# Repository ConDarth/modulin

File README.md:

# Modulin

This repository holds all data for th modulin I am building. The concept behind this design is to make a fully analog synthesizer using only standard components, with a fun control system based on a violin. This project is mostly based on a design Martin Molin of Wintergatan. An explanation of his design can be found [here](https://www.youtube.com/watch?v=MUdWeBYe3GY). 

My goal in improving this design is to make it more accessible. His design uses 9 or so prebuilt modules meant for modular synthesizers, each of which costs in the range of 70$+ making the instrument quite expensive for a diy build. I took inspiration from the modular synth DIY community to instead try and build the necessary modules from scratch using only much cheaper standard electronics components. The components I am limiting myself to are resistors, capacitors, inductors/transformers, diodes, transistors (both BJT and FET), op amps and linear voltage regulators.

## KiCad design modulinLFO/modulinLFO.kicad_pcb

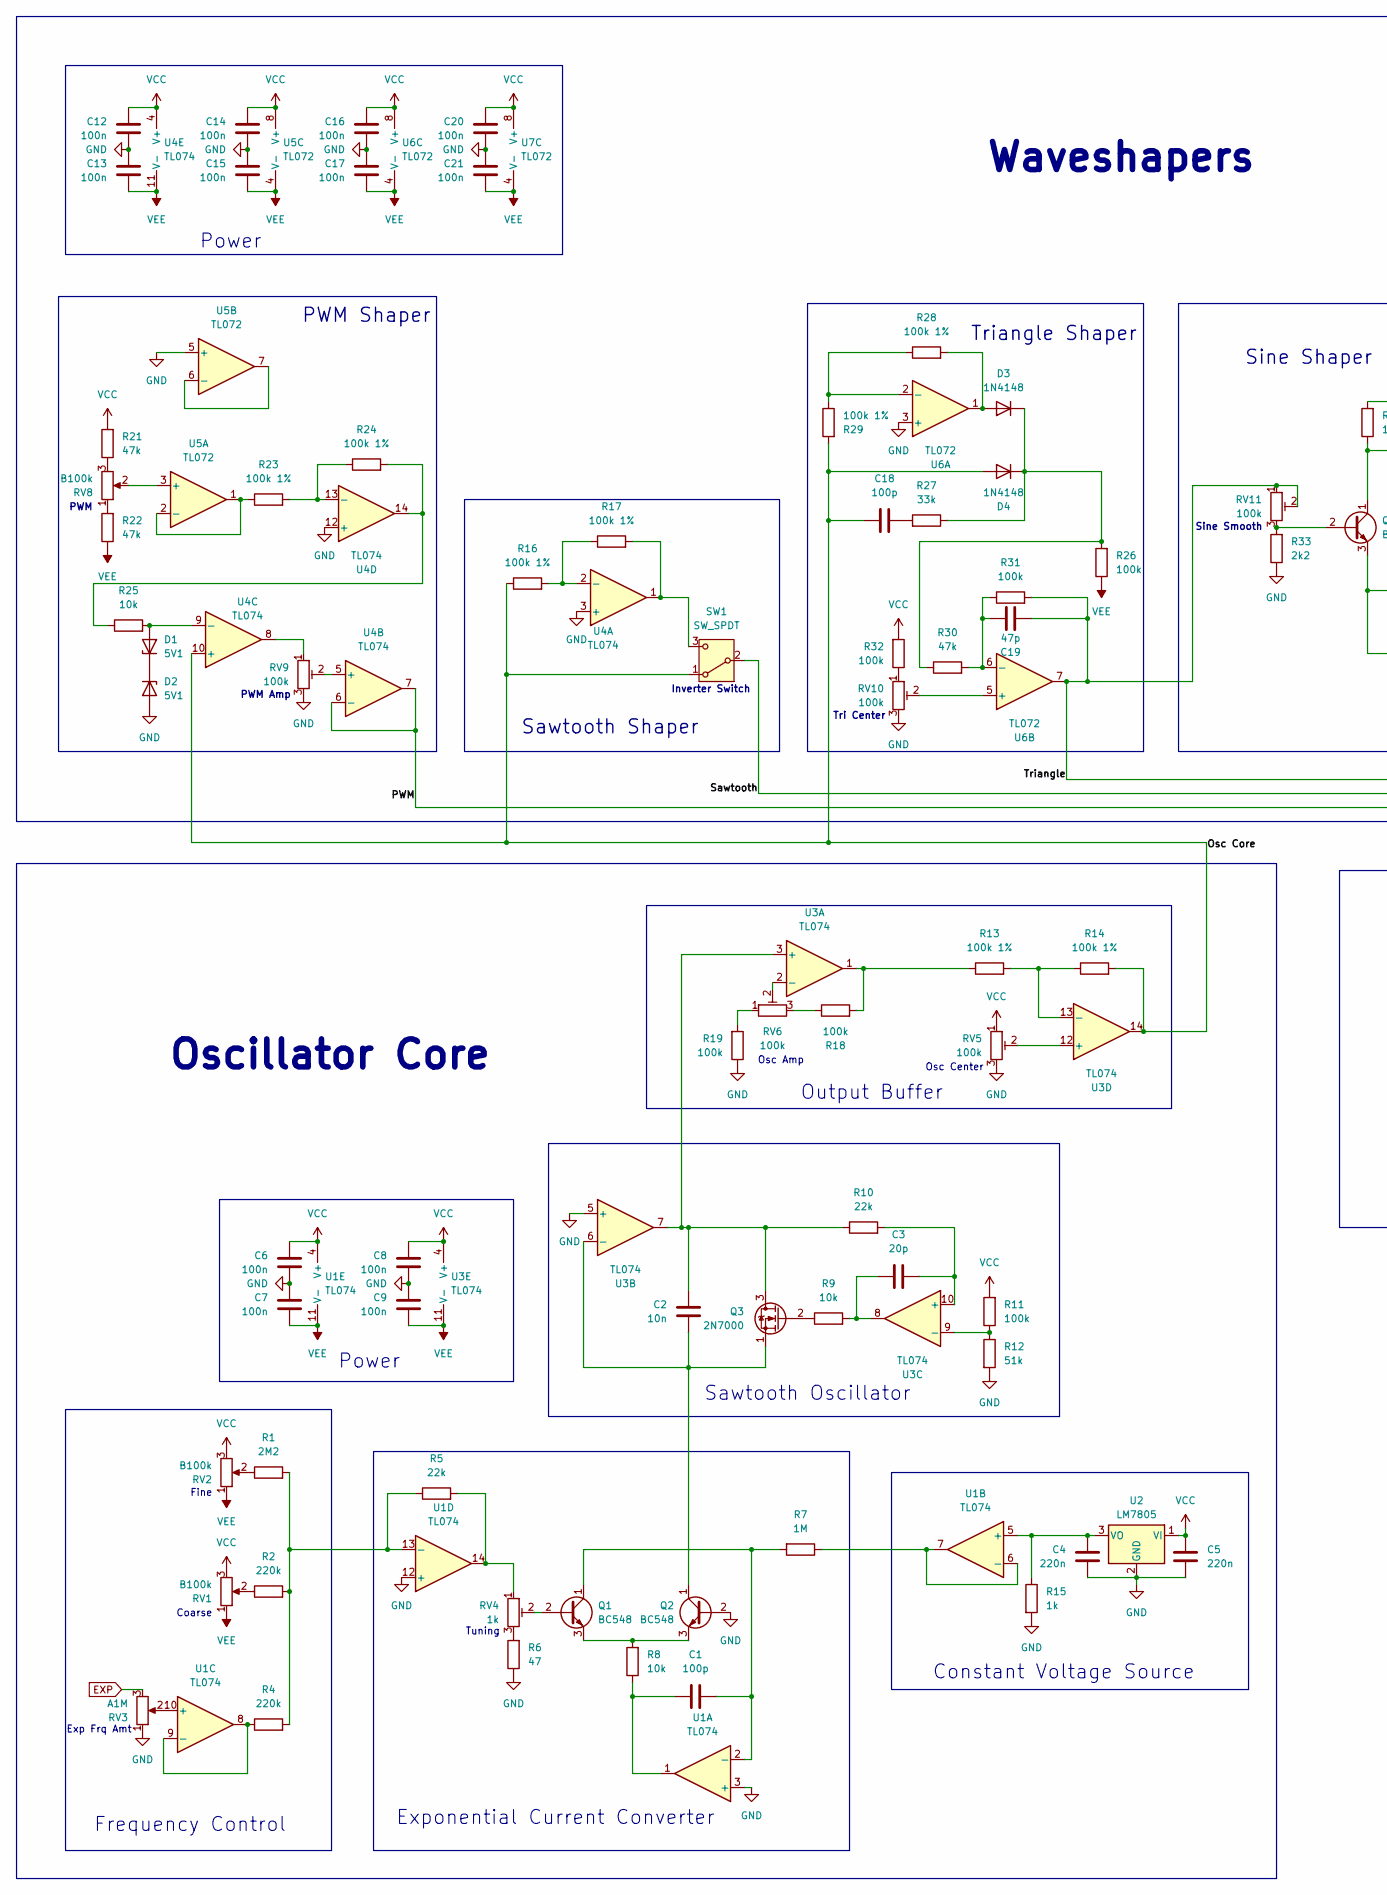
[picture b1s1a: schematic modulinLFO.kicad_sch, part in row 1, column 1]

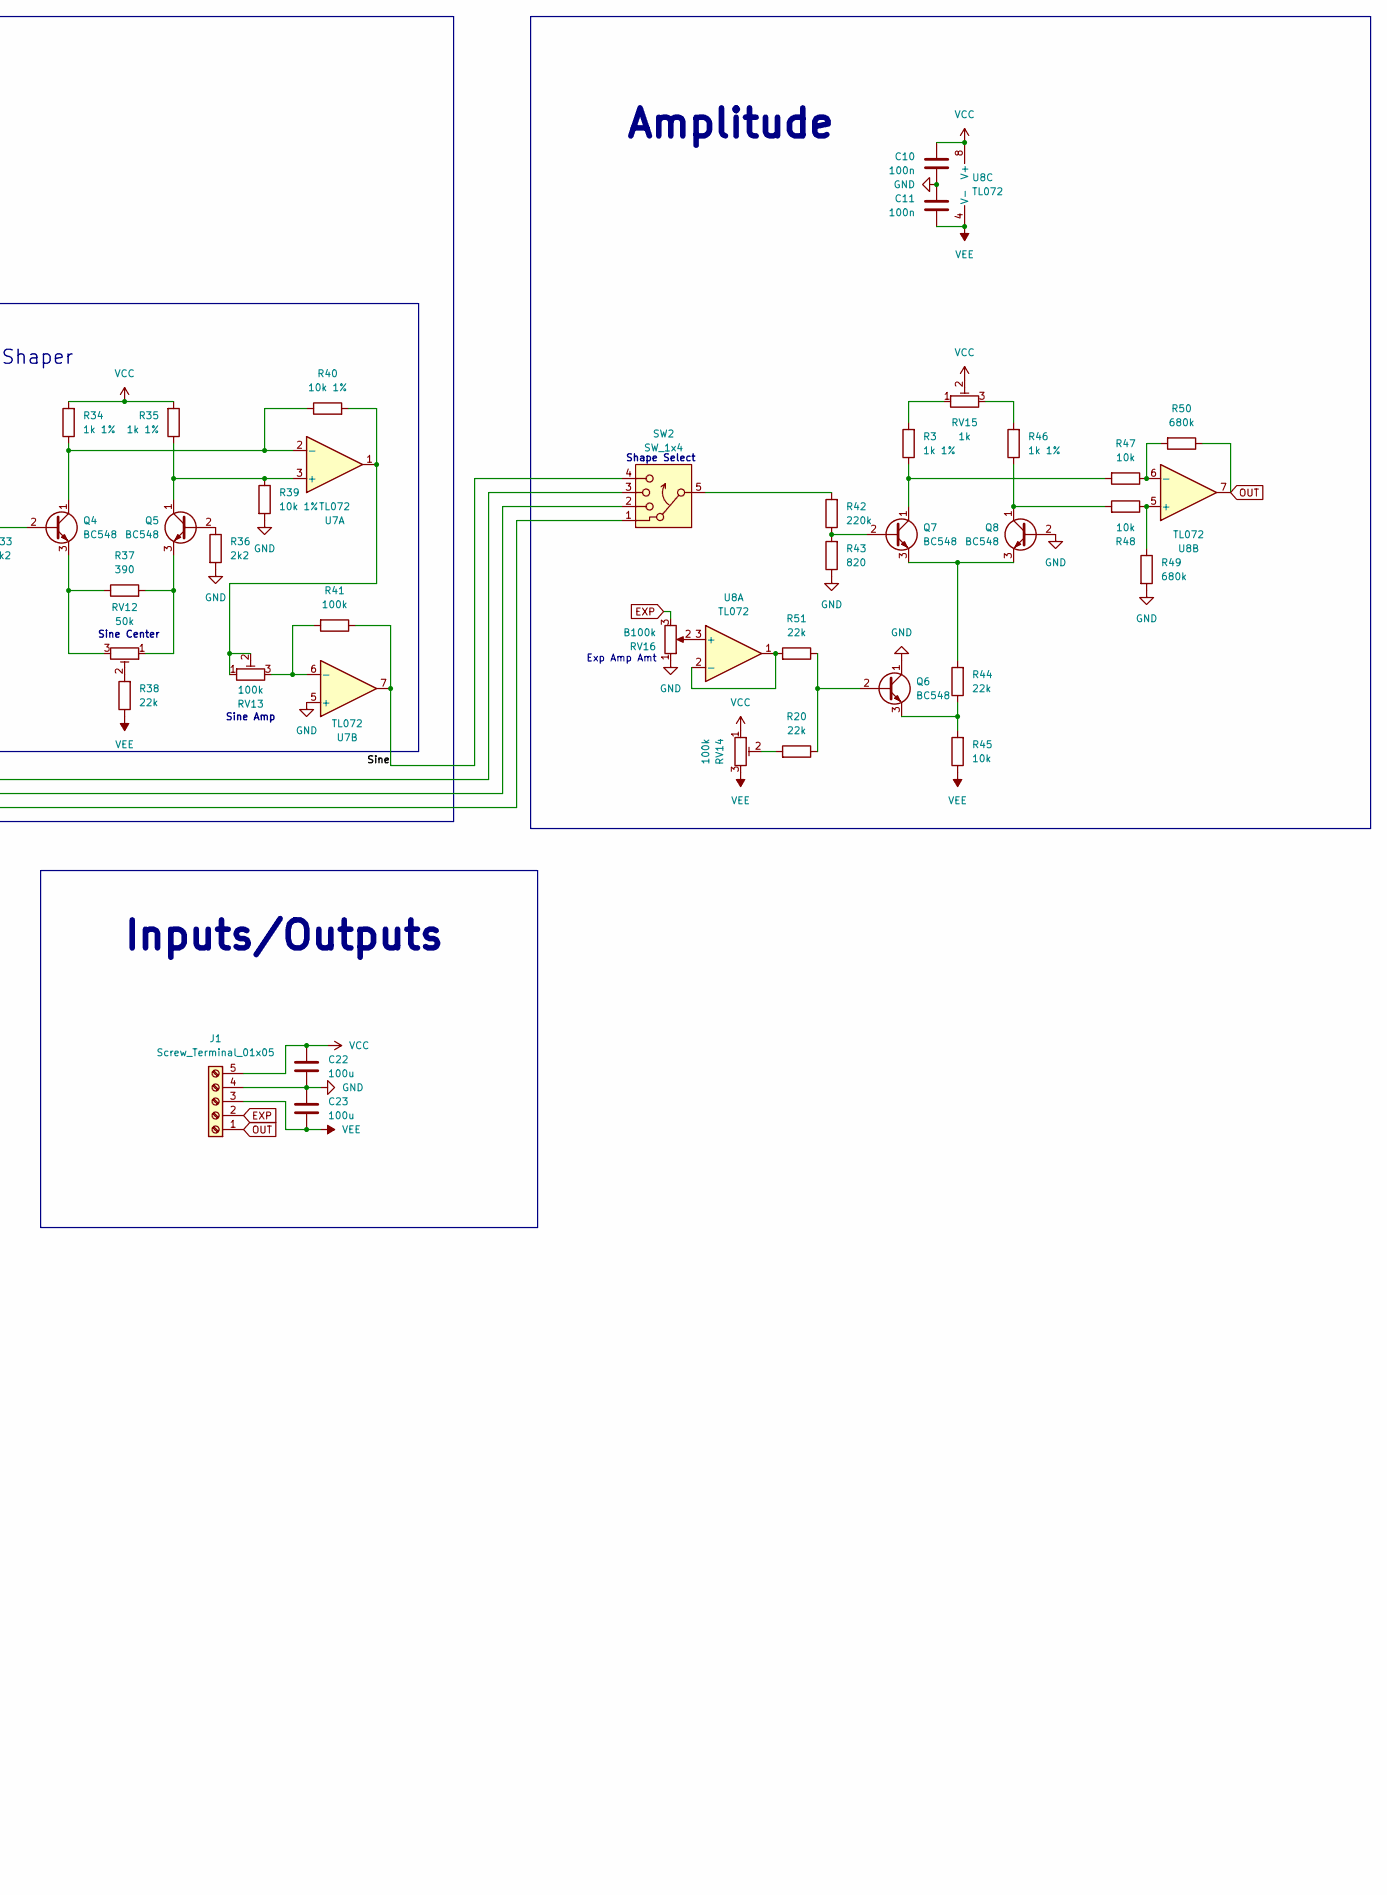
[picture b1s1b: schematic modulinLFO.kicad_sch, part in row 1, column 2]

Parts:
C1: 100p; C_Axial_P5.00mm_CNC
C2: 10n; C_Rect_P5.00mm_CNC
C3: 20p; C_Axial_P5.00mm_CNC
C4, C5: 220n; C_Axial_P5.00mm_CNC
C6, C7, C8, C9, C10, C11, C12, C13, C14, C15, C16, C17, C20, C21: 100n; C_Axial_P5.00mm_CNC
C18: 100p; C_Rect_P5.00mm_CNC
C19: 47p; C_Rect_P5.00mm_CNC
C22, C23: 100u; C_Radial_Polarized_P2.5mm_CNC
D1: 5V1; D_P2.54mm_CNC
D2: 5V1; D_P5.08mm_CNC
D3, D4: 1N4148; D_P7.62mm_CNC
J1: Screw_Terminal_01x05; TerminalBlock_1x5_CNC
Q1, Q2, Q4, Q5, Q6, Q7, Q8: BC548; TO-92_CNC
Q3: 2N7000; TO-92_CNC
R1: 2M2; R_10.16mm_CNC
R2, R42: 220k; R_10.16mm_CNC
R3, R46: 1k 1%; R_7.62mm_CNC
R4: 220k; R_2.54mm_CNC
R5: 22k; R_2.54mm_CNC
R6: 47; R_5.08mm_CNC
R7: 1M; R_10.16mm_CNC
R8, R9, R25, R45, R47, R48: 10k; R_10.16mm_CNC
R10, R38, R44, R51: 22k; R_10.16mm_CNC
R11: 100k; R_7.62mm_CNC
R12: 51k; R_5.08mm_CNC
R13, R16, R23: 100k 1%; R_10.16mm_CNC
R14, R17, R24, R28: 100k 1%; R_2.54mm_CNC
R15: 1k; R_7.62mm_CNC
R18, R31: 100k; R_2.54mm_CNC
R19, R41: 100k; R_2.54mm_CNC_Alt
R20: 22k; R_7.62mm_CNC
R21: 47k; R_7.62mm_CNC
R22, R30: 47k; R_10.16mm_CNC
R26, R32: 100k; R_10.16mm_CNC
R27: 33k; R_2.54mm_CNC_Alt
R29: 100k 1%; R_7.62mm_CNC
R33, R36: 2k2; R_10.16mm_CNC
R34, R35: 1k 1%; R_10.16mm_CNC
R37: 390; R_5.08mm_CNC
R39: 10k 1%; R_10.16mm_CNC
R40: 10k 1%; R_2.54mm_CNC_Alt
R43: 820; R_10.16mm_CNC
R49: 680k; R_10.16mm_CNC
R50: 680k; R_7.62mm_CNC
RV1, RV2, RV8, RV16: B100k; Potentiometer_PanelMount_CNC
RV3: A1M; Potentiometer_PanelMount_CNC
RV4, RV15: 1k; Potentiometer_Trim_CNC
RV5, RV6, RV9, RV10, RV11, RV13, RV14: 100k; Potentiometer_Trim_CNC
RV12: 50k; Potentiometer_Trim_CNC
SW1: SW_SPDT; SW_Slide_SPDT_H6.00mm_CNC
SW2: SW_1x4; SW_Slide_SP4T_H6.00mm_CNC
U1, U3, U4: TL074; DIP-14_CNC
U2: LM7805; TO-220_CNC
U5, U6, U7, U8: TL072; DIP-8_CNC

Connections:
/Osc Core: C18.1, D4.2 (A), R14.2, R16.1, R29.2, SW1.1 (A), U3.14, U4.10 (+)
/PWM: SW2.1, U4.6 (-), U4.7
/Sawtooth: SW1.2 (B), SW2.2
/Sine: R41.1, SW2.4, U7.7
/Triangle: C19.2, R31.2, RV11.1, RV11.2, SW2.3, U6.7
EXP: J1.2, RV3.3, RV16.3
GND: C4.1, C5.1, C6.2, C7.1, C8.2, C9.1, C10.2, C11.1, C12.2, C13.1, C14.2, C15.1, C16.2, C17.1, C20.2, C21.1, C22.1, C23.2, D2.2 (A), J1.4, Q2.2 (B), Q6.1 (C), Q8.2 (B), R6.1, R12.2, R15.2, R19.1, R33.1, R36.2, R39.2, R43.1, R49.2, RV3.1, RV5.3, RV9.3, RV10.3, RV16.1, U1.3 (+), U1.12 (+), U2.2 (GND), U3.5 (+), U4.3 (+), U4.12 (+), U5.5 (+), U6.3 (+), U7.5 (+)
unnamed: C1.1, R8.1, U1.1
unnamed: C3.1, R9.2, U3.8
unnamed: C18.2, R27.2
unnamed: D1.2 (A), R25.2, U4.9 (-)
unnamed: D1.1 (K), D2.1 (K)
unnamed: D3.2 (A), R28.2, U6.1
unnamed: D3.1 (K), D4.1 (K), R26.2, R27.1, R30.1
unnamed: Q1.2 (B), RV4.2
unnamed: C1.2, Q1.1 (C), R7.2, U1.2 (-)
unnamed: Q1.3 (E), Q2.3 (E), R8.2
unnamed: C2.2, Q2.1 (C), Q3.1 (S), U3.6 (-)
unnamed: C2.1, Q3.3 (D), R10.1, U3.3 (+), U3.7
unnamed: Q3.2 (G), R9.1
unnamed: Q4.2 (B), R33.2, RV11.3
unnamed: Q4.1 (C), R34.1, R40.1, U7.2 (-)
unnamed: Q4.3 (E), R37.1, RV12.3
unnamed: Q5.2 (B), R36.1
unnamed: Q5.1 (C), R35.1, R39.1, U7.3 (+)
unnamed: Q5.3 (E), R37.2, RV12.1
unnamed: Q6.2 (B), R20.1, R51.1
unnamed: Q6.3 (E), R44.1, R45.2
unnamed: Q7.2 (B), R42.1, R43.2
unnamed: Q7.1 (C), R3.1, R47.2
unnamed: Q7.3 (E), Q8.3 (E), R44.2
unnamed: Q8.1 (C), R46.1, R48.2
unnamed: R1.1, RV2.2
unnamed: R2.1, RV1.2
unnamed: R3.2, RV15.1
unnamed: R5.2, RV4.1, U1.14
unnamed: R6.2, RV4.3
unnamed: R13.1, R18.2, U3.1
unnamed: R18.1, RV6.3
unnamed: R19.2, RV6.1
unnamed: R20.2, RV14.2
unnamed: R21.1, RV8.3
unnamed: R22.2, RV8.1
unnamed: R24.2, R25.1, U4.14
unnamed: R32.1, RV10.1
unnamed: R38.2, RV12.2
unnamed: R40.2, RV13.1, RV13.2, U7.1
unnamed: R42.2, SW2.5
unnamed: R46.2, RV15.3
unnamed: RV9.1, U4.8
unnamed: R17.2, SW1.3 (C), U4.1
unnamed: C4.2, R15.1, U1.5 (+), U2.3 (VO)
unnamed: R7.1, U1.6 (-), U1.7
unnamed: RV3.2, U1.10 (+)
unnamed: R4.1, U1.8, U1.9 (-)
unnamed: R1.2, R2.2, R4.2, R5.1, U1.13 (-)
unnamed: RV6.2, U3.2 (-)
unnamed: C3.2, R10.2, U3.10 (+)
unnamed: R11.1, R12.1, U3.9 (-)
unnamed: RV5.2, U3.12 (+)
unnamed: R13.2, R14.1, U3.13 (-)
unnamed: R16.2, R17.1, U4.2 (-)
unnamed: RV9.2, U4.5 (+)
unnamed: R23.2, R24.1, U4.13 (-)
unnamed: RV8.2, U5.3 (+)
unnamed: R23.1, U5.1, U5.2 (-)
unnamed: U5.6 (-), U5.7
unnamed: R28.1, R29.1, U6.2 (-)
unnamed: RV10.2, U6.5 (+)
unnamed: C19.1, R30.2, R31.1, U6.6 (-)
unnamed: R41.2, RV13.3, U7.6 (-)
unnamed: RV16.2, U8.3 (+)
unnamed: R51.2, U8.1, U8.2 (-)
unnamed: R48.1, R49.1, U8.5 (+)
unnamed: R47.1, R50.2, U8.6 (-)
OUT: J1.1, R50.1, U8.7
VCC: C5.2, C6.1, C8.1, C10.1, C12.1, C14.1, C16.1, C20.1, C22.2, J1.5, R11.2, R21.2, R32.2, R34.2, R35.2, RV1.3, RV2.3, RV5.1, RV14.1, RV15.2, U1.4 (V+), U2.1 (VI), U3.4 (V+), U4.4 (V+), U5.8 (V+), U6.8 (V+), U7.8 (V+), U8.8 (V+)
VEE: C7.2, C9.2, C11.2, C13.2, C15.2, C17.2, C21.2, C23.1, J1.3, R22.1, R26.1, R38.1, R45.1, RV1.1, RV2.1, RV14.3, U1.11 (V-), U3.11 (V-), U4.11 (V-), U5.4 (V-), U6.4 (V-), U7.4 (V-), U8.4 (V-)

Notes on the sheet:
Constant Voltage Source
Power
Sine Amp
Triangle Shaper
PWM Shaper
Tuning
Exp Frq Amt
Output Buffer
Inputs/Outputs
Shape Select
Sine Shaper
Sawtooth Shaper
Inverter Switch
Tri Center
PWM Amp
Osc Center
Exponential Current Converter
Fine
Coarse
Oscillator Core
Osc Amp
Waveshapers
Sine Smooth
Sine Center
Amplitude
Sawtooth Oscillator
Exp Amp Amt
Frequency Control
PWM

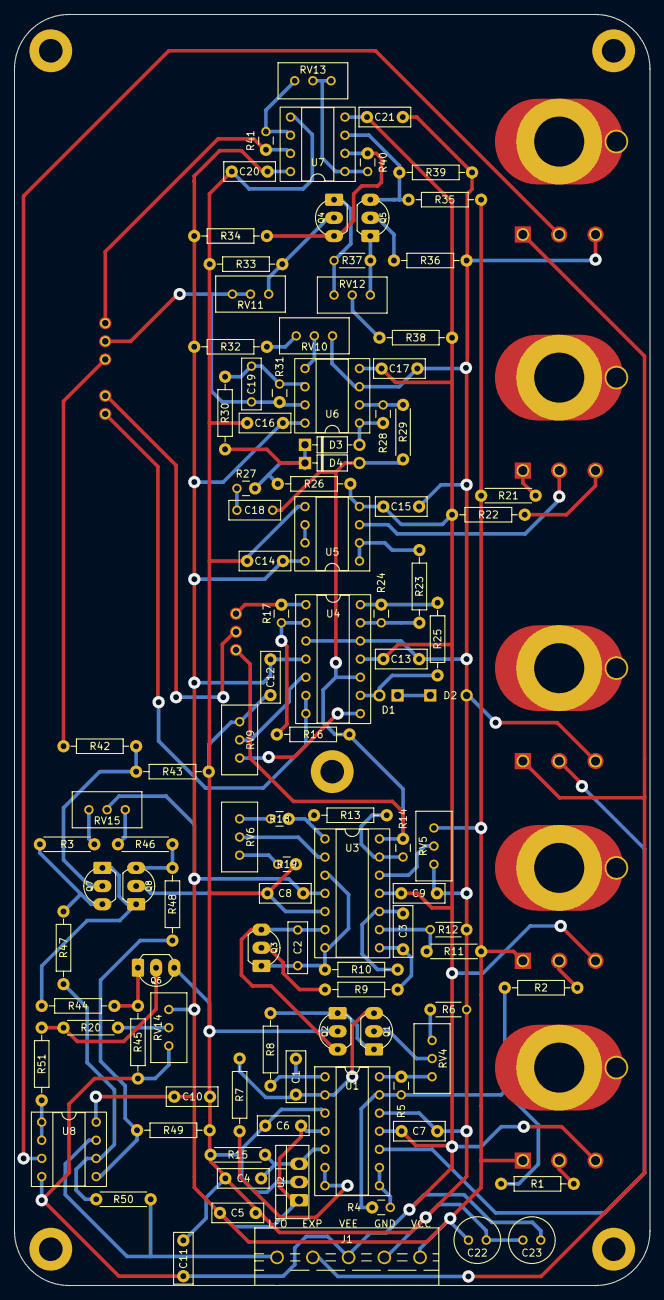
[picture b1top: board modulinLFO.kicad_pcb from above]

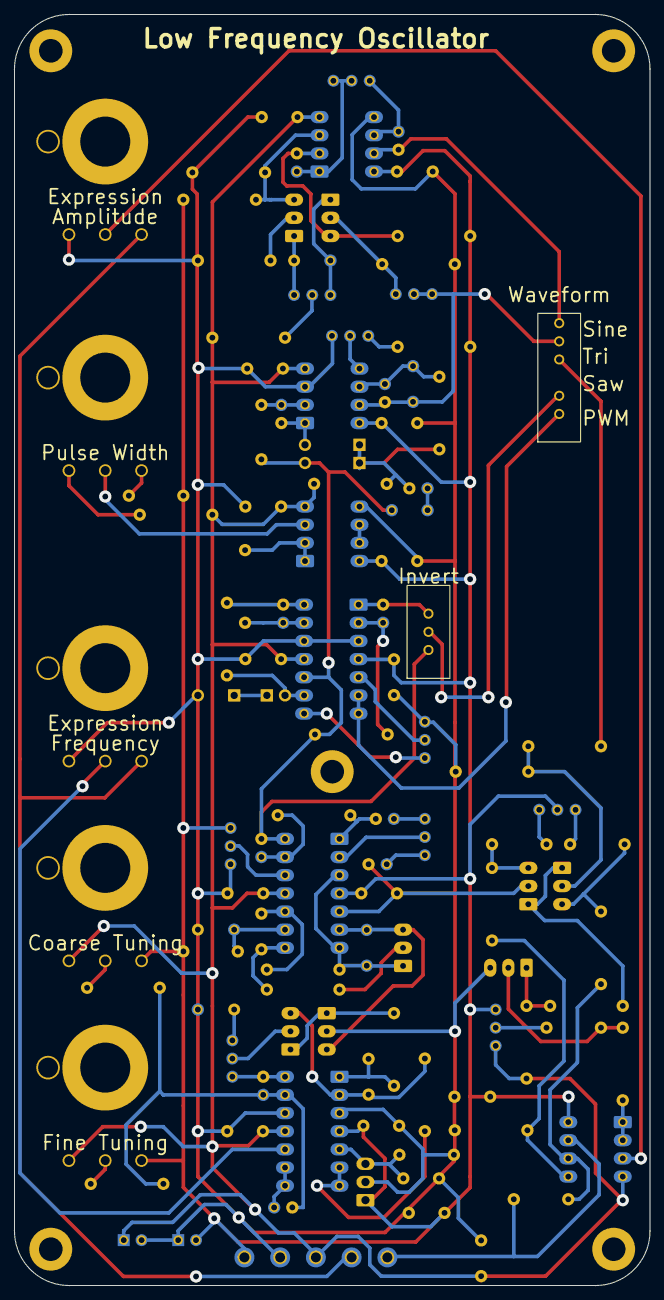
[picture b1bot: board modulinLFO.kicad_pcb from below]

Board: 2 copper layers, 88.9 x 177.8 mm, 112 parts (7 on the bottom side), 78 nets.

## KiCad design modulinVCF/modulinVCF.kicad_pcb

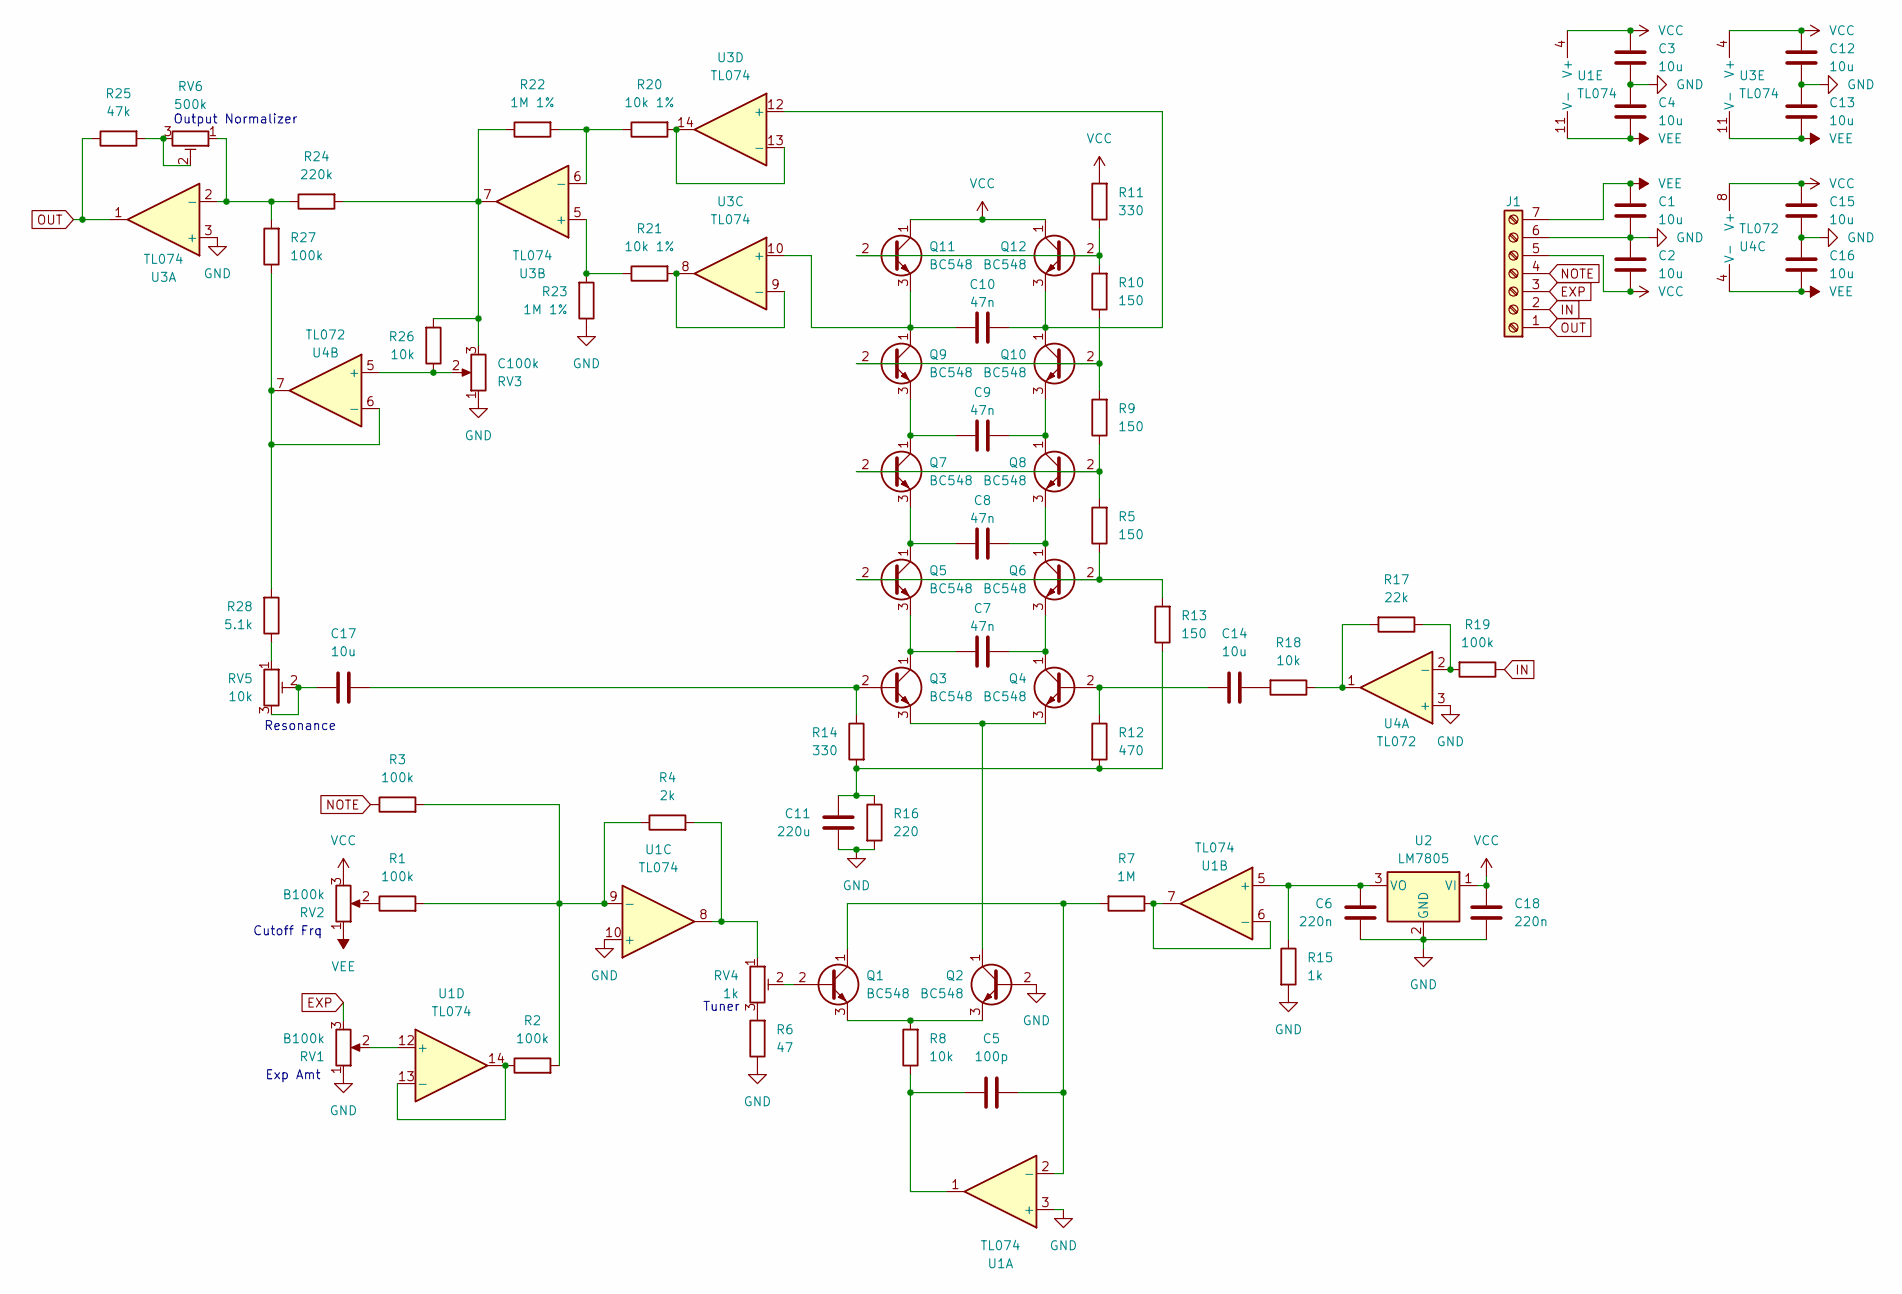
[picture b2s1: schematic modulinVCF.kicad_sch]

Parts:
C1, C2, C12: 10u; C_Rect_P5.00mm_CNC
C3, C4, C13, C14, C15, C16, C17: 10u; C_Axial_P5.00mm_CNC
C5: 100p; C_Axial_P5.00mm_CNC
C6, C18: 220n; C_Axial_P5.00mm_CNC
C7, C8, C9, C10: 47n; C_Axial_P5.00mm_CNC
C11: 220u; CP_Radial_D8.0mm_P3.80mm
J1: Screw_Terminal_01x07; TerminalBlock_1x7_CNC
Q1, Q2, Q3, Q4, Q5, Q6, Q7, Q8, Q9, Q10, Q11, Q12: BC548; TO-92_CNC
R1, R2, R3, R19, R27: 100k; R_10.16mm_CNC
R4: 2k; R_2.54mm_CNC
R5, R9, R10: 150; R_7.62mm_CNC
R6: 47; R_5.08mm_CNC
R7: 1M; R_10.16mm_CNC
R8: 10k; R_7.62mm_CNC
R11: 330; R_2.54mm_CNC
R12: 470; R_2.54mm_CNC_Alt
R13: 150; R_2.54mm_CNC
R14: 330; R_7.62mm_CNC
R15: 1k; R_7.62mm_CNC
R16: 220; R_10.16mm_CNC
R17: 22k; R_2.54mm_CNC
R18: 10k; R_5.08mm_CNC
R20, R21: 10k 1%; R_10.16mm_CNC
R22: 1M 1%; R_2.54mm_CNC
R23: 1M 1%; R_7.62mm_CNC
R24: 220k; R_10.16mm_CNC
R25: 47k; R_10.16mm_CNC
R26: 10k; R_10.16mm_CNC
R28: 5.1k; R_2.54mm_CNC
RV1, RV2: B100k; Potentiometer_PanelMount_CNC
RV3: C100k; Potentiometer_PanelMount_CNC
RV4: 1k; Potentiometer_Trim_CNC
RV5: 10k; Potentiometer_Trim_CNC
RV6: 500k; Potentiometer_Trim_CNC
U1, U3: TL074; DIP-14_CNC
U2: LM7805; TO-220_CNC
U4: TL072; DIP-8_CNC

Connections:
EXP: J1.3, RV1.3
GND: C1.2, C2.1, C3.2, C4.1, C6.1, C11.1, C12.2, C13.1, C15.2, C16.1, C18.1, J1.6, Q2.2 (B), R6.1, R15.2, R16.2, R23.1, RV1.1, RV3.1, U1.3 (+), U1.10 (+), U2.2 (GND), U3.3 (+), U4.3 (+)
IN: J1.2, R19.1
NOTE: J1.4, R3.1
unnamed: C5.1, R8.1, U1.1
unnamed: C11.2, R12.2, R13.1, R14.2, R16.1
unnamed: C14.1, R18.2
unnamed: C17.2, RV5.2, RV5.3
unnamed: Q1.2 (B), RV4.2
unnamed: C5.2, Q1.1 (C), R7.2, U1.2 (-)
unnamed: Q1.3 (E), Q2.3 (E), R8.2
unnamed: Q2.1 (C), Q3.3 (E), Q4.3 (E)
unnamed: C17.1, Q3.2 (B), R14.1
unnamed: C7.2, Q3.1 (C), Q5.3 (E)
unnamed: C14.2, Q4.2 (B), R12.1
unnamed: C7.1, Q4.1 (C), Q6.3 (E)
unnamed: Q5.2 (B), Q6.2 (B), R5.1, R13.2
unnamed: C8.2, Q5.1 (C), Q7.3 (E)
unnamed: C8.1, Q6.1 (C), Q8.3 (E)
unnamed: Q7.2 (B), Q8.2 (B), R5.2, R9.1
unnamed: C9.2, Q7.1 (C), Q9.3 (E)
unnamed: Q9.2 (B), Q10.2 (B), R9.2, R10.1
unnamed: C10.1, Q10.1 (C), Q12.3 (E), U3.12 (+)
unnamed: C9.1, Q8.1 (C), Q10.3 (E)
unnamed: Q11.2 (B), Q12.2 (B), R10.2, R11.1
unnamed: C10.2, Q9.1 (C), Q11.3 (E), U3.10 (+)
unnamed: R1.1, RV2.2
unnamed: R4.2, RV4.1, U1.8
unnamed: R6.2, RV4.3
unnamed: R17.2, R18.1, U4.1
unnamed: R22.1, R24.2, R26.2, RV3.3, U3.7
unnamed: R25.2, RV6.2, RV6.3
unnamed: R28.1, RV5.1
unnamed: C6.2, R15.1, U1.5 (+), U2.3 (VO)
unnamed: R7.1, U1.6 (-), U1.7
unnamed: R1.2, R2.2, R3.2, R4.1, U1.9 (-)
unnamed: RV1.2, U1.12 (+)
unnamed: R2.1, U1.13 (-), U1.14
unnamed: R24.1, R27.2, RV6.1, U3.2 (-)
unnamed: R21.1, R23.2, U3.5 (+)
unnamed: R20.1, R22.2, U3.6 (-)
unnamed: R21.2, U3.8, U3.9 (-)
unnamed: R20.2, U3.13 (-), U3.14
unnamed: R17.1, R19.2, U4.2 (-)
unnamed: R26.1, RV3.2, U4.5 (+)
unnamed: R27.1, R28.2, U4.6 (-), U4.7
OUT: J1.1, R25.1, U3.1
VCC: C2.2, C3.1, C12.1, C15.1, C18.2, J1.5, Q11.1 (C), Q12.1 (C), R11.2, RV2.3, U1.4 (V+), U2.1 (VI), U3.4 (V+), U4.8 (V+)
VEE: C1.1, C4.2, C13.2, C16.2, J1.7, RV2.1, U1.11 (V-), U3.11 (V-), U4.4 (V-)

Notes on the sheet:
Output Normalizer
Resonance
Tuner
Exp Amt
Cutoff Frq

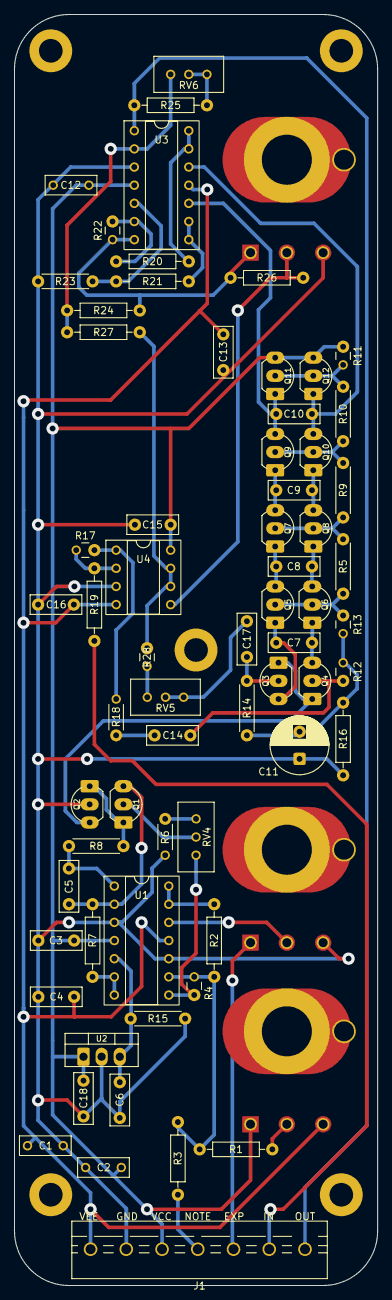
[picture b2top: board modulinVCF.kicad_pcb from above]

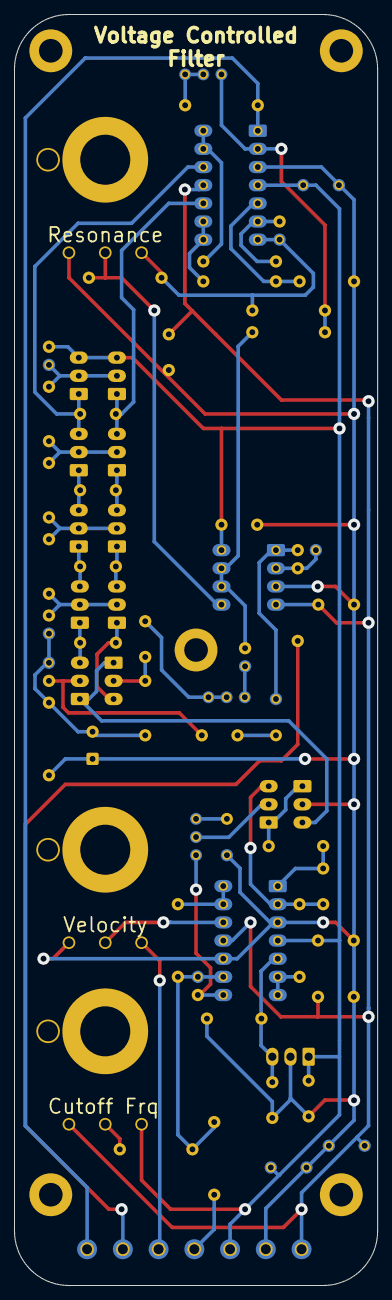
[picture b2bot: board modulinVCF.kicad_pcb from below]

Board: 2 copper layers, 50.8 x 177.8 mm, 69 parts (3 on the bottom side), 49 nets.

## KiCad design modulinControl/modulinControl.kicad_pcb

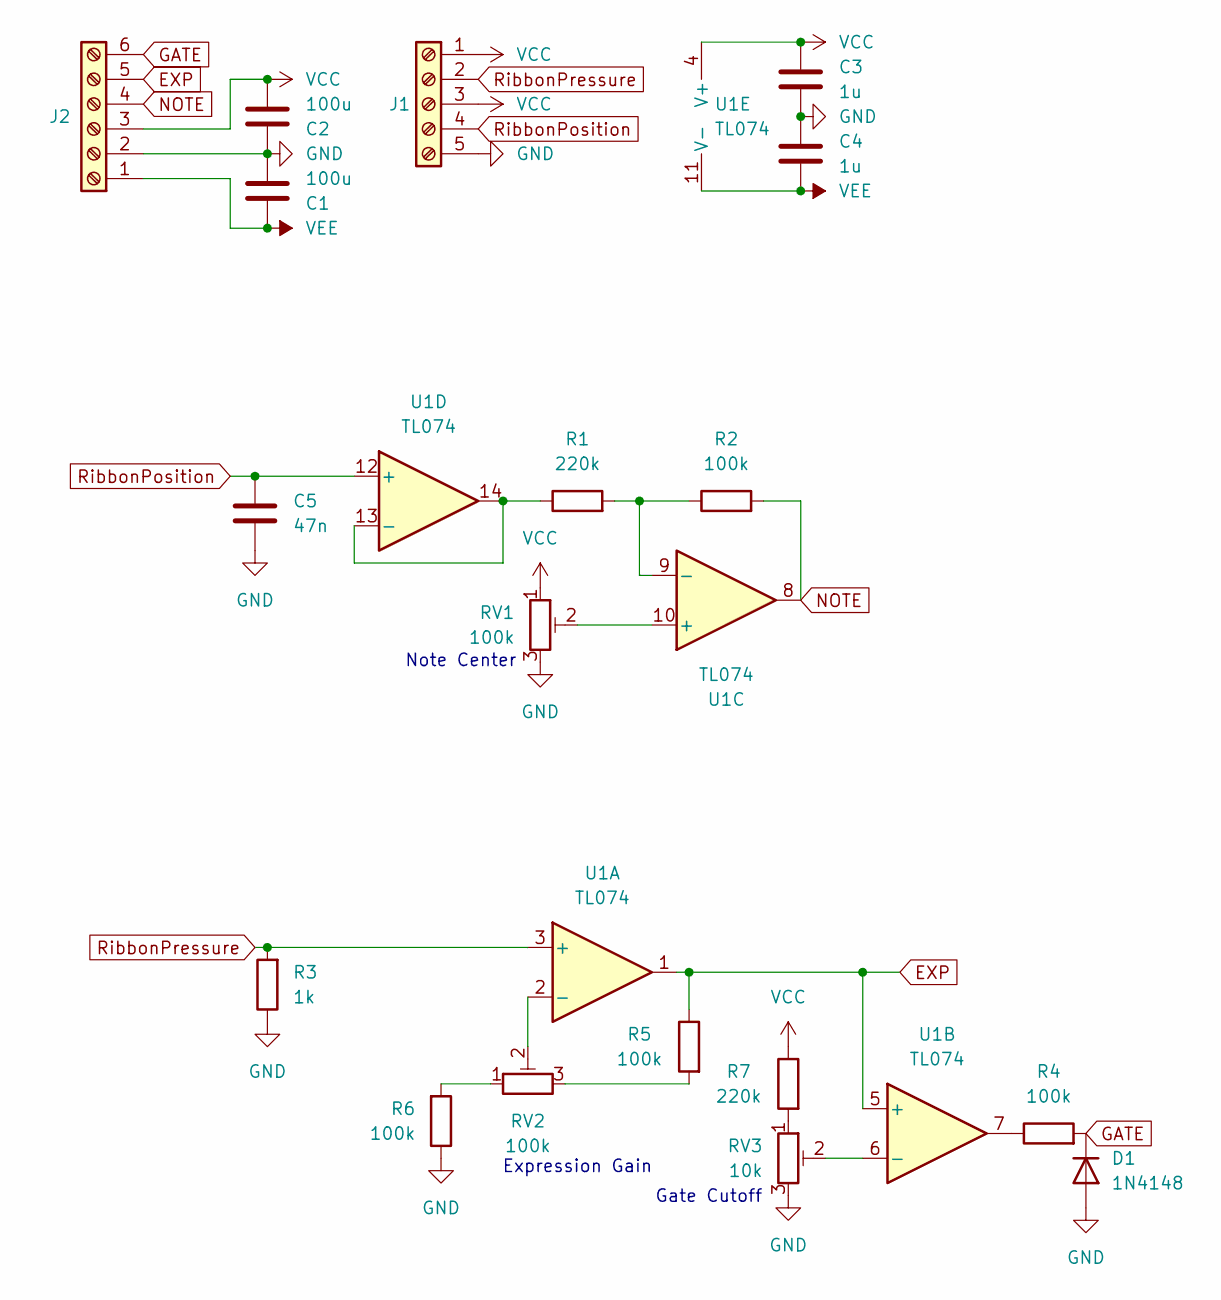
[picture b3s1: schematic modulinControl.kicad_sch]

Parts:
C1, C2: 100u; C_Radial_Polarized_P3.8mm_CNC
C3, C4: 1u; C_Axial_P5.00mm_CNC
C5: 47n; C_Axial_P5.00mm_CNC
D1: 1N4148; D_P7.62mm_CNC
J1: Screw_Terminal_01x05; TerminalBlock_1x5_CNC
J2: Screw_Terminal_01x06; TerminalBlock_1x6_CNC
R1, R7: 220k; R_10.16mm_CNC
R2, R4, R5, R6: 100k; R_10.16mm_CNC
R3: 1k; R_10.16mm_CNC
RV1, RV2: 100k; Potentiometer_Trim_CNC
RV3: 10k; Potentiometer_Trim_CNC
U1: TL074; DIP-14_CNC

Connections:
EXP: J2.5, R5.1, U1.1, U1.5 (+)
GATE: D1.1 (K), J2.6, R4.2
GND: C1.2, C2.1, C3.2, C4.1, C5.2, D1.2 (A), J1.5, J2.2, R3.1, R6.1, RV1.3, RV3.3
NOTE: J2.4, R2.2, U1.8
unnamed: R4.1, U1.7
unnamed: R5.2, RV2.3
unnamed: R6.2, RV2.1
unnamed: R7.2, RV3.1
unnamed: RV2.2, U1.2 (-)
unnamed: RV3.2, U1.6 (-)
unnamed: RV1.2, U1.10 (+)
unnamed: R1.2, R2.1, U1.9 (-)
unnamed: R1.1, U1.13 (-), U1.14
RibbonPosition: C5.1, J1.4, U1.12 (+)
RibbonPressure: J1.2, R3.2, U1.3 (+)
VCC: C2.2, C3.1, J1.1, J1.3, J2.3, R7.1, RV1.1, U1.4 (V+)
VEE: C1.1, C4.2, J2.1, U1.11 (V-)

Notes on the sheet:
Note Center
Gate Cutoff
Expression Gain

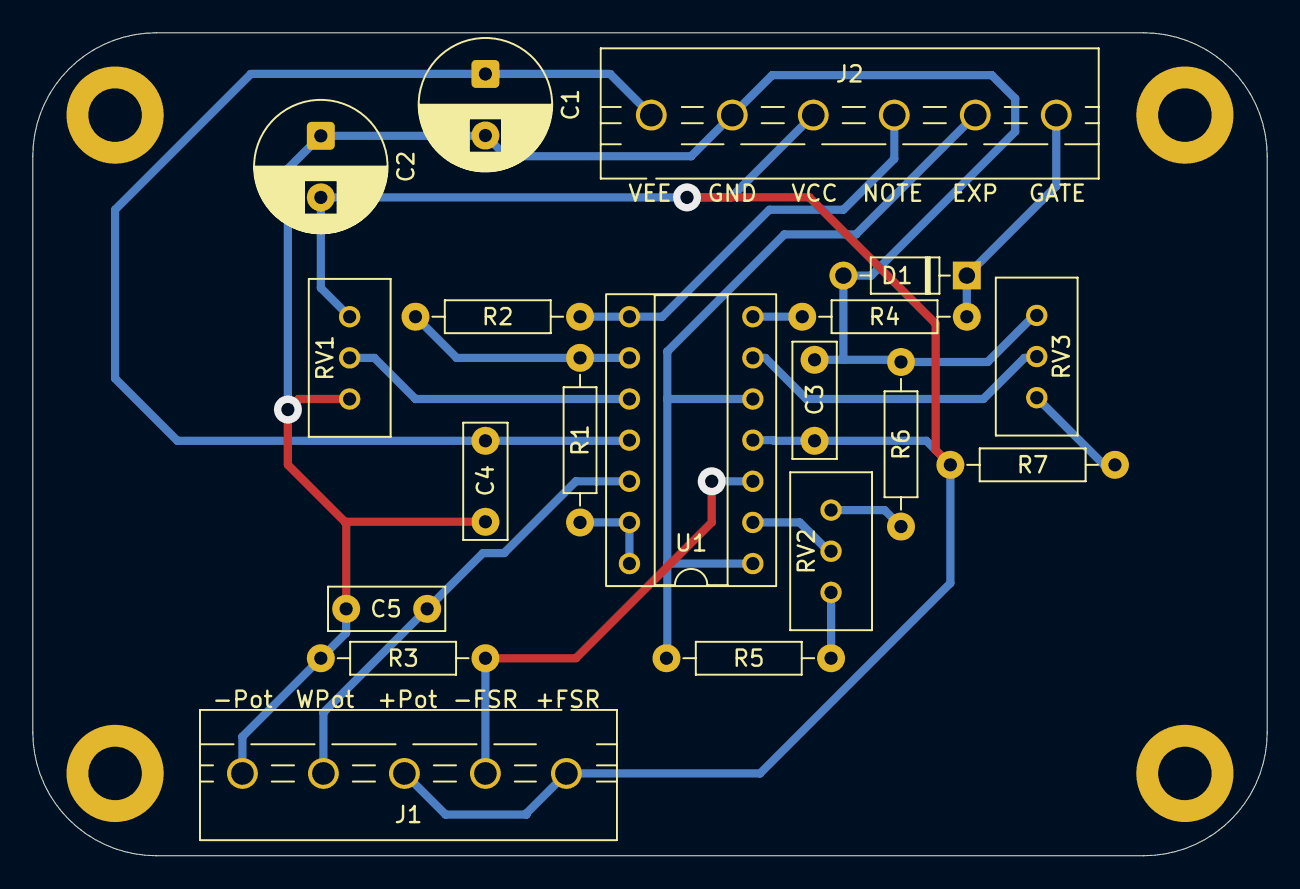
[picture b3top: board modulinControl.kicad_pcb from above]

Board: 2 copper layers, 76.2 x 50.8 mm, 19 parts (0 on the bottom side), 17 nets.

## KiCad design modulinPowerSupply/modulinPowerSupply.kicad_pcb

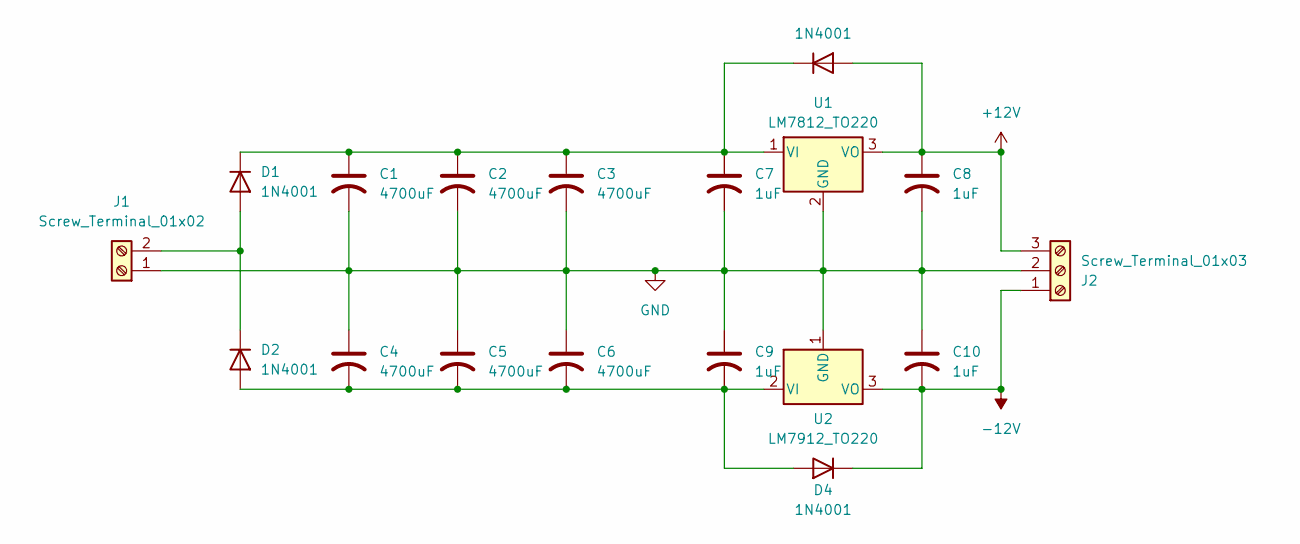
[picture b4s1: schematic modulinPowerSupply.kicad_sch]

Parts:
C1, C2, C3, C4, C5, C6: 4700uF; C_Radial_Polarized_P7.50mm_CNC
C7, C8, C9, C10: 1uF; C_Rect_P5.00mm_CNC
D1, D2, D3, D4: 1N4001; D_P10.16mm_CNC
J1: Screw_Terminal_01x02; TerminalBlock_1x2_CNC
J2: Screw_Terminal_01x03; TerminalBlock_1x3_CNC
U1: LM7812_TO220; TO-220_CNC
U2: LM7912_TO220; TO-220_CNC

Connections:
+12V: C8.1, D3.2 (A), J2.3, U1.3 (VO)
-12V: C10.2, D4.1 (K), J2.1, U2.3 (VO)
GND: C1.2, C2.2, C3.2, C4.1, C5.1, C6.1, C7.2, C8.2, C9.1, C10.1, J1.1, J2.2, U1.2 (GND), U2.1 (GND)
unnamed: D1.2 (A), D2.1 (K), J1.2
unnamed: C1.1, C2.1, C3.1, C7.1, D1.1 (K), D3.1 (K), U1.1 (VI)
unnamed: C4.2, C5.2, C6.2, C9.2, D2.2 (A), D4.2 (A), U2.2 (VI)

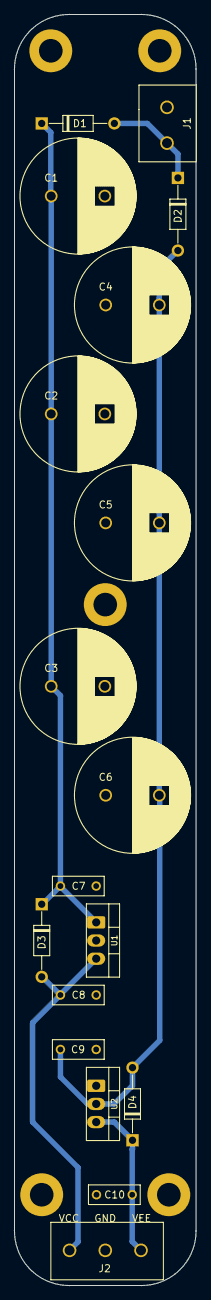
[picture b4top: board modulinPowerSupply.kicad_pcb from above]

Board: 2 copper layers, 25.4 x 177.8 mm, 18 parts (0 on the bottom side), 6 nets.
